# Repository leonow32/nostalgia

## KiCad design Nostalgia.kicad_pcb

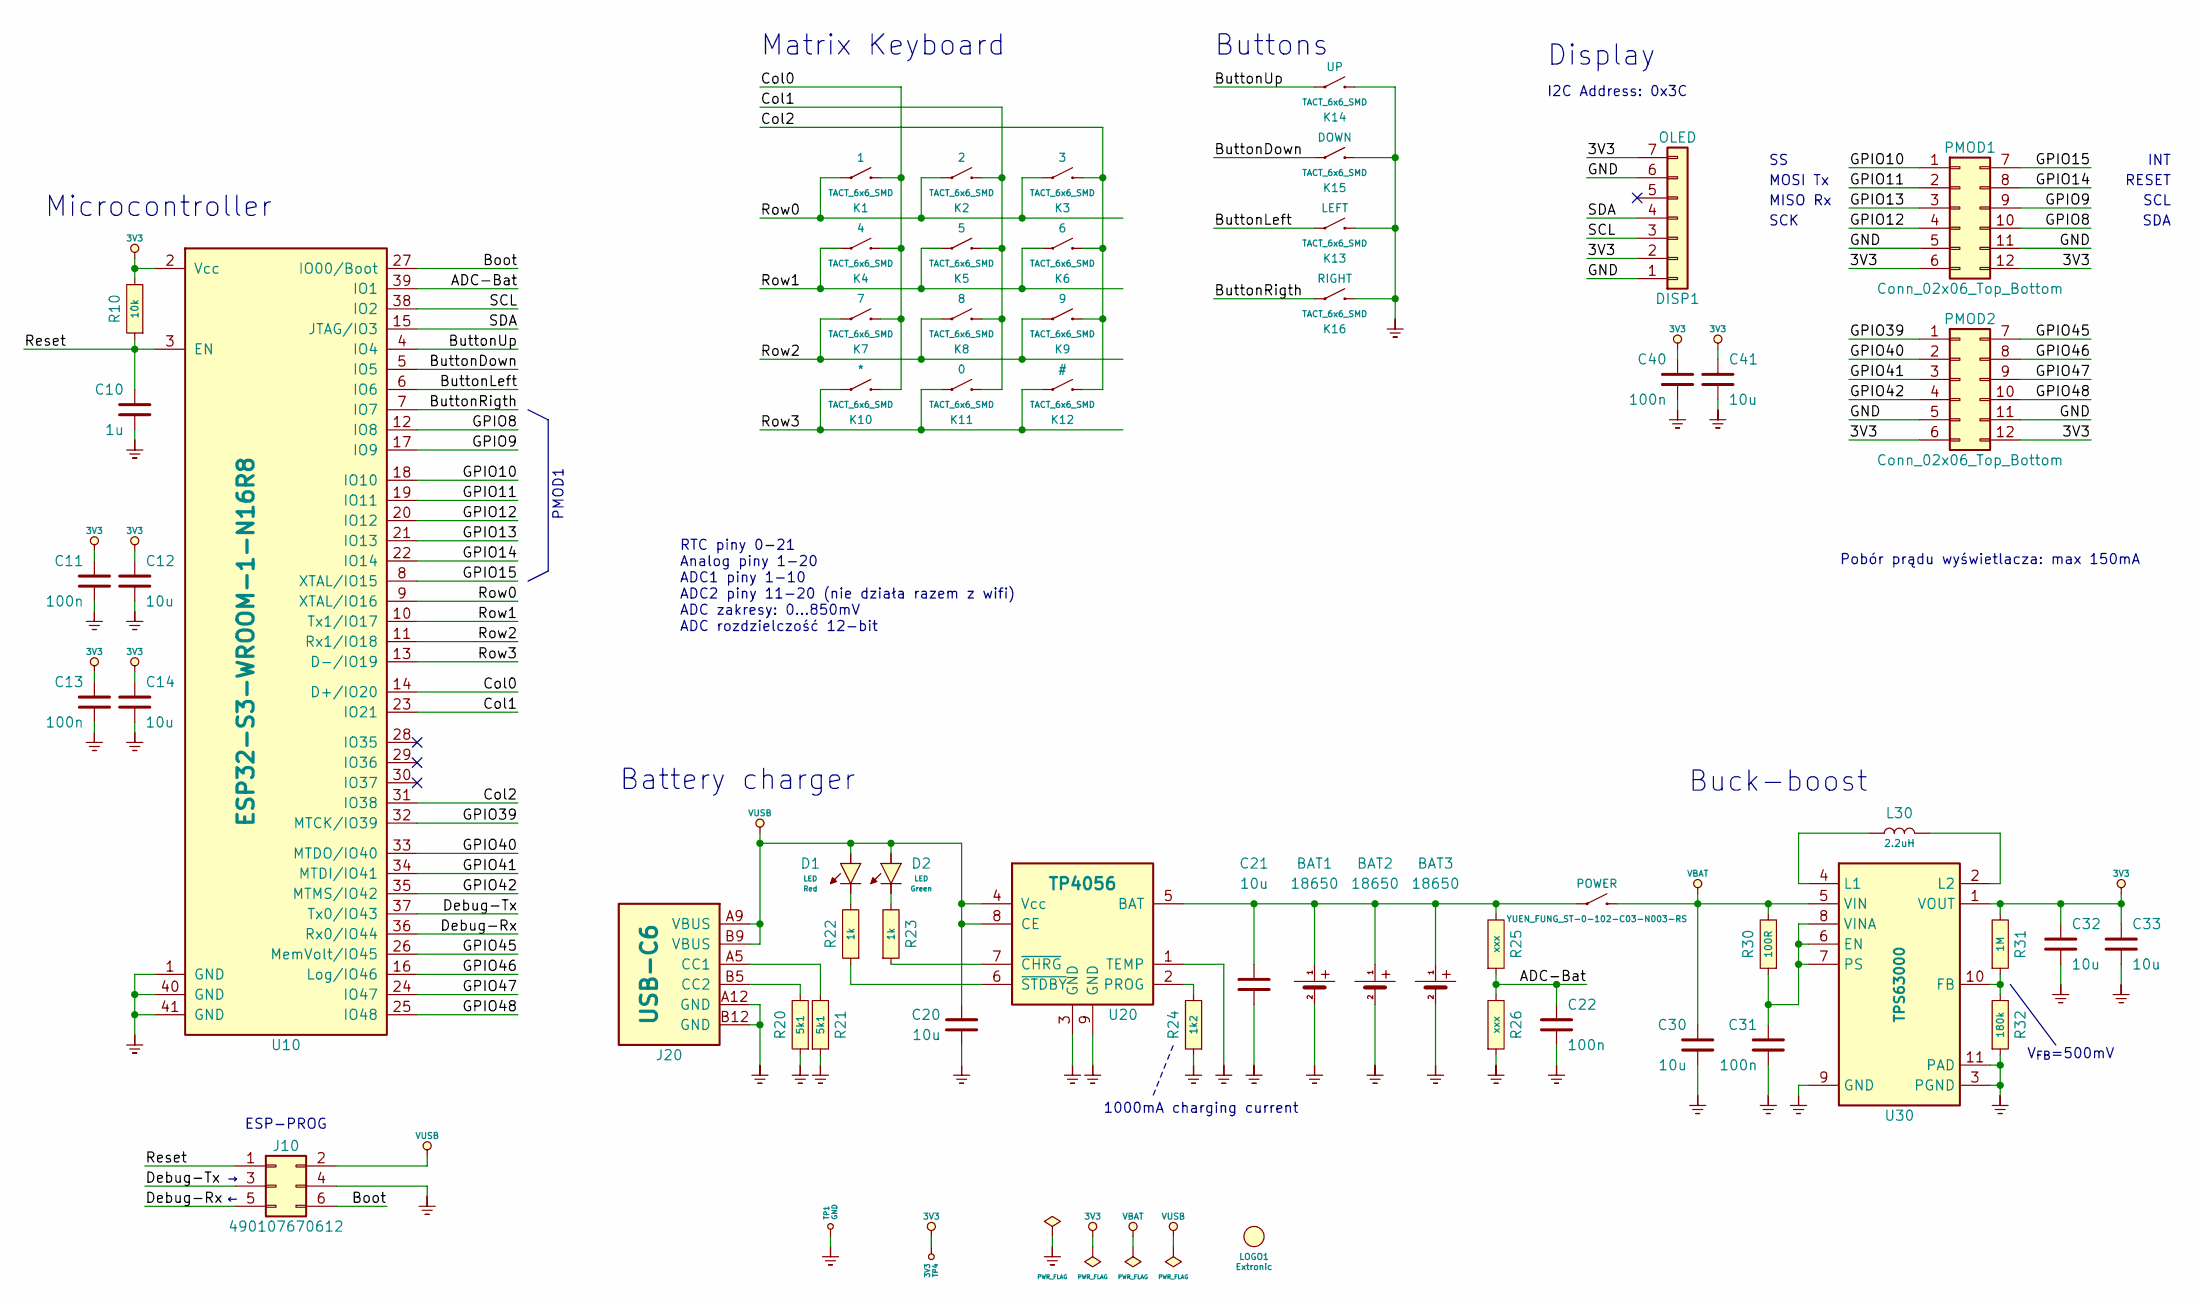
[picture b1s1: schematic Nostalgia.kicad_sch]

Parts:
BAT1, BAT2, BAT3: 18650; Bat_BH-18650-A1AJ005; Part MYOUNG BH-18650-A1AJ005
C10: 1u; C_0805
C11, C13, C22, C31, C40: 100n; C_0805
C12, C14, C20, C21, C30, C32, C33, C41: 10u; C_0805
D1, D2: LED; LED_0805
DISP1: OLED; OLED_2.42inch_board_3
J10: 490107670612; Wurth_490107670612
J20: USB-C6; Part USB4125-GF-A
K1, K2, K3, K4, K5, K6, K7, K8, K9, K10, K11, K12, K13, K14, K15, K16: TACT_6x6_SMD
K17: YUEN_FUNG_ST-0-102-C03-N003-RS
L30: 2.2uH; DJNR5050
LOGO1: Extronic; Extronic-mask-20mm-bez-www
PMOD1, PMOD2: Conn_02x06_Top_Bottom; PMOD
R10: 10k; R_0805
R20, R21: 5k1; R_0805
R22, R23: 1k; R_0805
R24: 1k2; R_0805
R25, R26: xxx; R_0805
R30: 100R; R_0805
R31: 1M; R_0805
R32: 180k; R_0805
TP1: GND; Testpoint_2.00mm
TP4: 3V3; Testpoint_2.00mm
U10: ESP32-S3-WROOM-1-N16R8; ESP32-S3-WROOM-1
U20: TP4056; SO8-PowerPad; Part TP4056 UMW
U30: TPS63000; Texas_DRC0010J_ThermalVias

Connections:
3V3: C11.1, C12.1, C13.1, C14.1, C32.1, C33.1, C40.1, C41.1, DISP1.2, DISP1.7, PMOD1.6, PMOD1.12, PMOD2.6, PMOD2.12, R10.2, R31.2, TP4.1, U10.2 (Vcc), U30.1 (VOUT)
/ADC-Bat: C22.1, R25.1, R26.2, U10.39 (IO1)
/Boot: J10.6, U10.27 (IO00/Boot)
/ButtonDown: K15.2, U10.5 (IO5)
/ButtonLeft: K13.2, U10.6 (IO6)
/ButtonRigth: K16.2, U10.7 (IO7)
/ButtonUp: K14.2, U10.4 (IO4)
/Col0: K1.1, K4.1, K7.1, K10.1, U10.14 (D+/IO20)
/Col1: K2.1, K5.1, K8.1, K11.1, U10.23 (IO21)
/Col2: K3.1, K6.1, K9.1, K12.1, U10.31 (IO38)
/Debug-Rx: J10.5, U10.36 (Rx0/IO44)
/Debug-Tx: J10.3, U10.37 (Tx0/IO43)
/GPIO8: PMOD1.10, U10.12 (IO8)
/GPIO9: PMOD1.9, U10.17 (IO9)
/GPIO10: PMOD1.1, U10.18 (IO10)
/GPIO11: PMOD1.2, U10.19 (IO11)
/GPIO12: PMOD1.4, U10.20 (IO12)
/GPIO13: PMOD1.3, U10.21 (IO13)
/GPIO14: PMOD1.8, U10.22 (IO14)
/GPIO15: PMOD1.7, U10.8 (XTAL/IO15)
/GPIO39: PMOD2.1, U10.32 (MTCK/IO39)
/GPIO40: PMOD2.2, U10.33 (MTDO/IO40)
/GPIO41: PMOD2.3, U10.34 (MTDI/IO41)
/GPIO42: PMOD2.4, U10.35 (MTMS/IO42)
/GPIO45: PMOD2.7, U10.26 (MemVolt/IO45)
/GPIO46: PMOD2.8, U10.16 (Log/IO46)
/GPIO47: PMOD2.9, U10.24 (IO47)
/GPIO48: PMOD2.10, U10.25 (IO48)
/Reset: C10.1, J10.1, R10.1, U10.3 (EN)
/Row0: K1.2, K2.2, K3.2, U10.9 (XTAL/IO16)
/Row1: K4.2, K5.2, K6.2, U10.10 (Tx1/IO17)
/Row2: K7.2, K8.2, K9.2, U10.11 (Rx1/IO18)
/Row3: K10.2, K11.2, K12.2, U10.13 (D-/IO19)
/SCL: DISP1.3, U10.38 (IO2)
/SDA: DISP1.4, U10.15 (JTAG/IO3)
GND: BAT1.2 (-), BAT2.2 (-), BAT3.2 (-), C10.2, C11.2, C12.2, C13.2, C14.2, C20.2, C21.2, C22.2, C30.2, C31.2, C32.2, C33.2, C40.2, C41.2, DISP1.1, DISP1.6, J10.4, J20.A12 (GND), J20.B12 (GND), K13.1, K14.1, K15.1, K16.1, PMOD1.5, PMOD1.11, PMOD2.5, PMOD2.11, R20.1, R21.1, R24.1, R26.1, R32.1, TP1.1, U10.1 (GND), U10.40 (GND), U10.41 (GND), U20.1 (TEMP), U20.3 (GND), U20.9 (GND), U30.3 (PGND), U30.9 (GND), U30.11 (PAD)
unnamed: BAT1.1 (+), BAT2.1 (+), BAT3.1 (+), C21.1, K17.2, R25.2, U20.5 (BAT)
unnamed: D1.1 (K), R22.2
unnamed: D2.1 (K), R23.2
unnamed: J20.A5 (CC1), R21.2
unnamed: J20.B5 (CC2), R20.2
unnamed: R24.2, U20.2 (PROG)
unnamed: R23.1, U20.7 (~CHRG)
unnamed: R22.1, U20.6 (~STDBY)
unnamed: C31.1, R30.1, U30.6 (EN), U30.7 (PS), U30.8 (VINA)
unnamed: R31.1, R32.2, U30.10 (FB)
unnamed: L30.1, U30.4 (L1)
unnamed: L30.2, U30.2 (L2)
VBAT: C30.1, K17.1, R30.2, U30.5 (VIN)
VUSB: C20.1, D1.2 (A), D2.2 (A), J10.2, J20.A9 (VBUS), J20.B9 (VBUS), U20.4 (Vcc), U20.8 (CE)

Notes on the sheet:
Pobór prądu wyświetlacza: max 150mA
SDA
PMOD1
V_{FB}=500mV
SCK
SCL
RTC piny 0-21 Analog piny 1-20 ADC1 piny 1-10 ADC2 piny 11-20 (nie działa razem z wifi) ADC zakresy: 0...850mV ADC rozdzielczość 12-bit
MOSI Tx
Microcontroller
Display
I2C Address: 0x3C
ESP-PROG
MISO Rx
1000mA charging current
Battery charger
Buck-boost
INT
Matrix Keyboard
Buttons
RESET

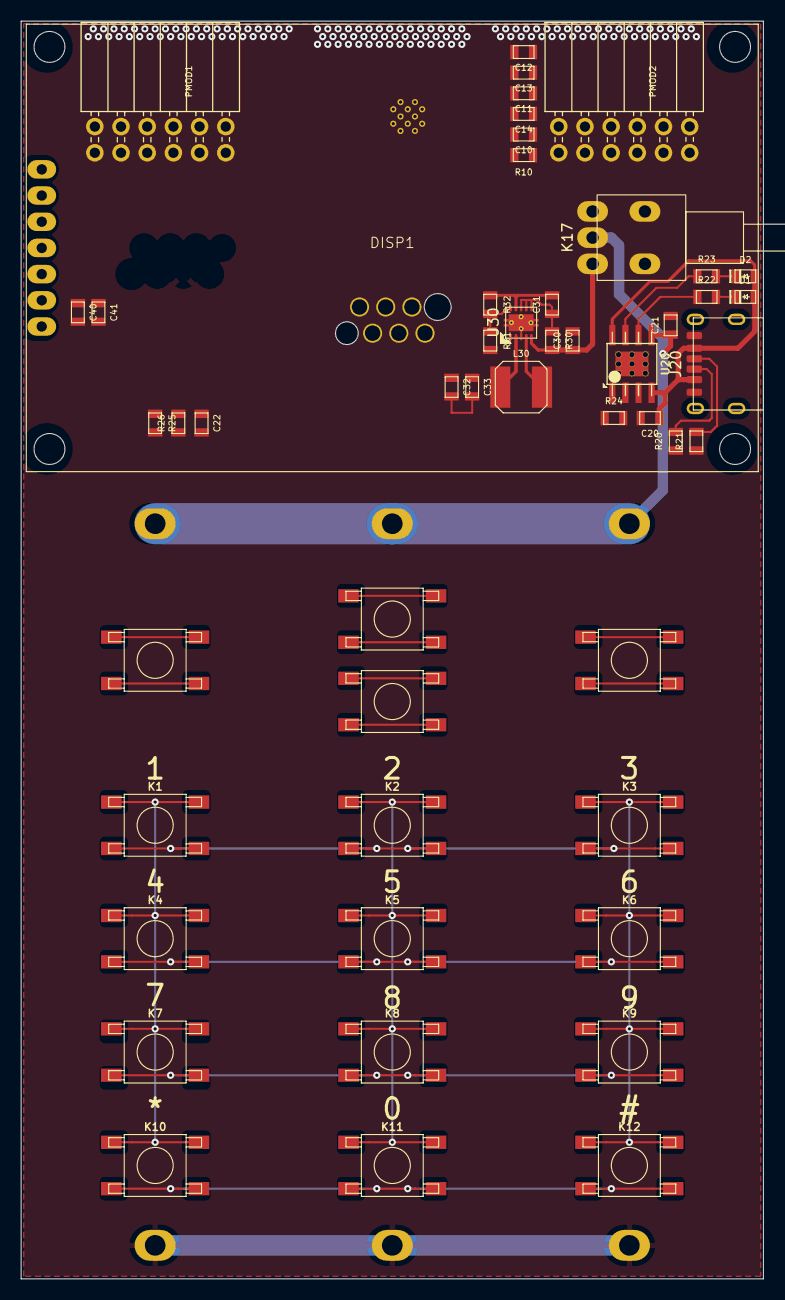
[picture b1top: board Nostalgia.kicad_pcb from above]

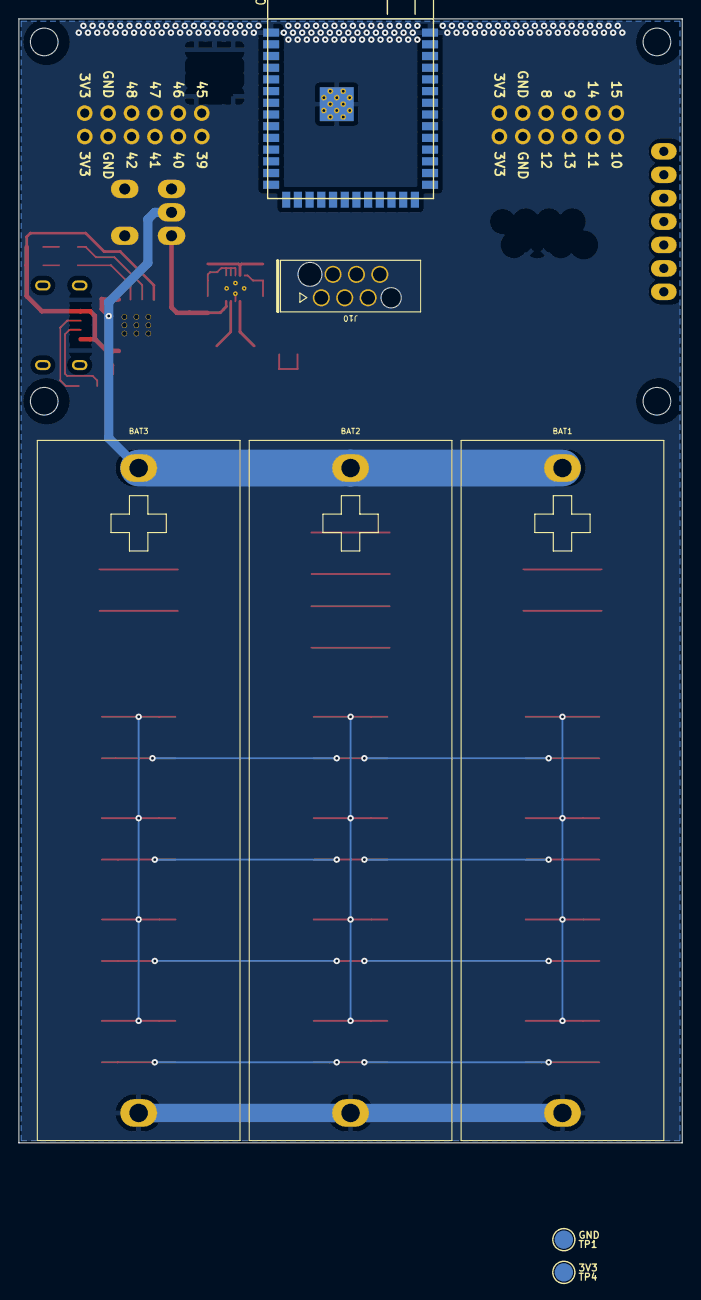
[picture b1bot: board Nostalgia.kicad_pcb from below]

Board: 2 copper layers, 72.0 x 122.0 mm, 59 parts (7 on the bottom side), 50 nets.

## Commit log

2025-01-15 gitignore
2025-01-15 Początek
2025-01-24 Schemat
2025-02-08 Schemat OLED 2.42"
2025-02-14 Kolejny schemat modułu 2.42"
2025-02-15 Wydłużenie płytki i zmiana przycisków z 6x3 na 6x6
2025-03-25 Schemat prawie gotowy
2025-03-27 Włącznik zasilania
2025-03-30 Projektowanie płytki
